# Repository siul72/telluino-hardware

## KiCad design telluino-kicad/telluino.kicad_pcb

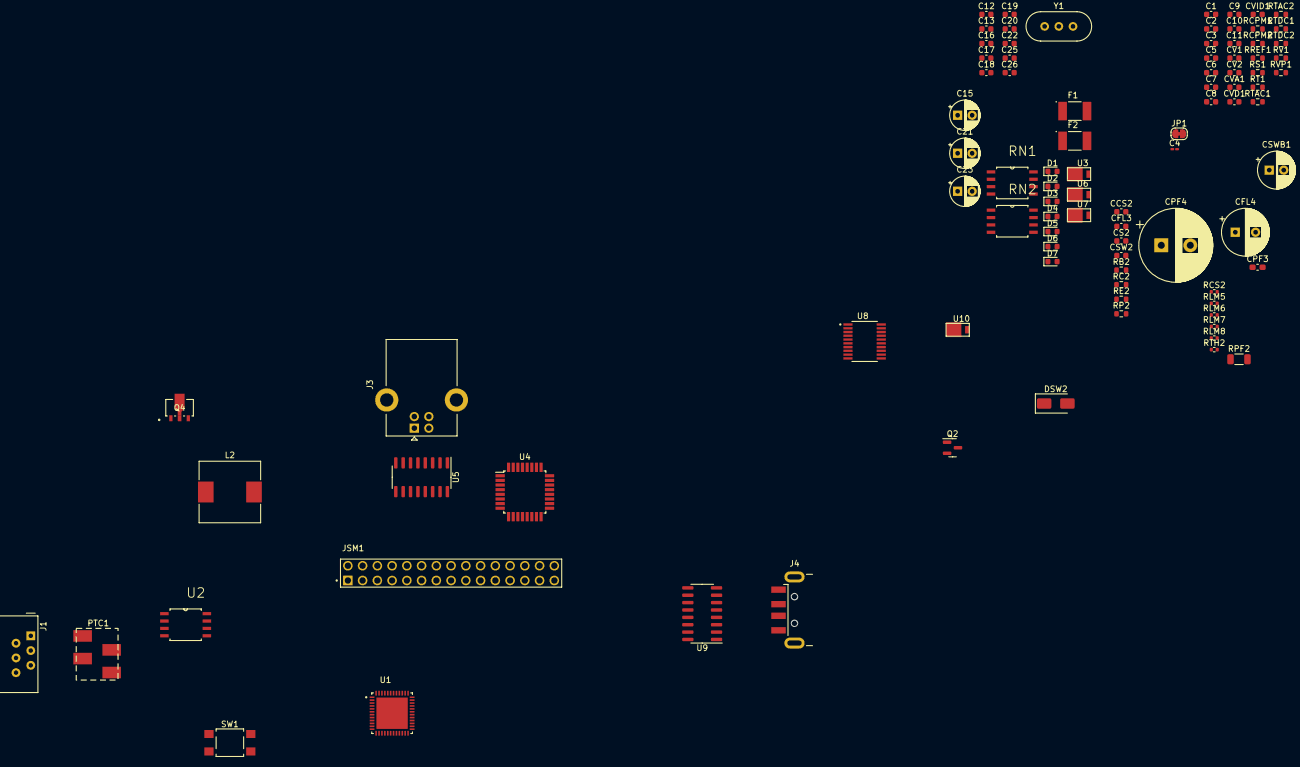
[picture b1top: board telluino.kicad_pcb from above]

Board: 2 copper layers, 92 parts (0 on the bottom side), 88 nets, no tracks yet.

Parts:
C1: 0.1 uF/100V; C_0603_1608Metric
C2, C3, C5, C6: 22 nF/100V; C_0603_1608Metric
C4: 22 nF/100V; C_0201_0603Metric_Pad0.64x0.40mm_HandSolder
C7, C11: 0.1 uF/16V; C_0603_1608Metric
C8, C9, C10: 4.7 uF/8.3V; C_0603_1608Metric
C12, C13, C25, C26: 0.1uF; C_0603_1608Metric
C15, C21, C23: 10uF_16V; CP_Radial_D5.0mm_P2.50mm
C16, C17, C22: 100nF; C_0603_1608Metric
C18, C19, C20: 1uF; C_0603_1608Metric
CCS2: 220pF; C_0603_1608Metric
CFL3: 0.1uF/100V; C_0603_1608Metric
CFL4: 10uF/100V; CP_Radial_D8.0mm_P3.50mm
CPF3: 0.1uF/100V; C_0603_1608Metric_Pad1.08x0.95mm_HandSolder
CPF4: 47uF/100V; CP_Radial_D12.5mm_P5.00mm
CS2: 100nF/25V; C_0603_1608Metric
CSW2: 10uF/25V; C_0603_1608Metric
CSWB1: 220uF/25V; CP_Radial_D6.3mm_P2.50mm
CV1: 4.7uF/8.3V; C_0603_1608Metric
CV2: 1uF/8.3V; C_0603_1608Metric
CVA1: 0.1uF/16V; C_0603_1608Metric
CVD1: 0.01uF/16V; C_0603_1608Metric
CVID1: 0.1uF/18V; C_0603_1608Metric
D1: PWR Green; LED_0603_1608Metric
D2, D4: Red Rx; LED_0603_1608Metric
D3, D6: Green Tx; LED_0603_1608Metric
D5: RUN Blue; LED_0603_1608Metric
D7: OP Orange; LED_0603_1608Metric
DSW2: ES1C-13-F 1A/150V; D_SMA
F1, F2: MF-MSMF050-2; FUSM4632X85
J1: 6P2C; RJ12_Amphenol_54601
J3: USB_B; USB_B_Lumberg_2411_02_Horizontal
J4: USB_A; USB_A_CNCTech_1001-011-01101_Horizontal
JP1: A_D_Ground_Bridge; SolderJumper-2_P1.3mm_Bridged_RoundedPad1.0x1.5mm
JSM1: 77313-101-30LF; AMPHENOL_77313-101-30LF
L2: 47uH 1.5A; L_10.4x10.4_H4.8
PTC1: MF-SD013; ptc-4-mf-sd
Q2: MMBT3904; SOT-23
Q4: ZXTP2012Z; SOT-89-3_4P5X2P6_DIO
RB2: 1K; R_0603_1608Metric
RC2: 75R; R_0603_1608Metric
RCPM1, RCPM2: 1Meg 1%; R_0603_1608Metric
RCS2: 3.48K; R_0402_1005Metric
RE2: 75R 5%; R_0603_1608Metric
RLM5, RLM6, RLM7, RLM8: 1R0 1/16W; R_0402_1005Metric
RN1, RN2: 4*1K; SOIC127P780X210-8N
RP2: 10K; R_0603_1608Metric
RPF2: 20R; R_1206_3216Metric
RREF1: 75K 0.5%; R_0603_1608Metric
RS1: 1Meg 1%; R_0603_1608Metric
RT1: 47.5K 1%; R_0603_1608Metric
RTAC1, RTAC2: 10K 1%; R_0603_1608Metric
RTDC1, RTDC2: 1Meg 1%; R_0603_1608Metric
RTH2: 1K; R_0402_1005Metric
RV1: 2R0 5%; R_0603_1608Metric
RVP1: 0; R_0603_1608Metric
SW1: SW_Push; SW_SPST_TL3305A
U1: LE9641PQC; QFN50P700X700X90-49N
U2: TISP61089BDR-S; SOIC127P780X210-8N
U3, U6, U7, U10: SS1P3L; DO220AAL
U4: ATmega328P-A; TQFP-32_7x7mm_P0.8mm
U5, U9: CH340C; SOIC-16_3.9x9.9mm_P1.27mm
U8: TXS0108EPWRG4; SOP65P640X120-20N
Y1: 16MHz; Crystal_HC49-U-3Pin_Vertical

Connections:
3.3V: CSWB1.1, CV1.2, CVD1.2, CVID1.2, JSM1.01, JSM1.02, RP2.1, RV1.1, U1.14 (VDDSW), U1.15 (DVDD), U1.23 (VDDHPI), U1.24 (*ZSI), U7.P$1 (K), U8.2 (VCCA), U8.10 (OE), U10.P$1 (K)
+3.3VA: C12.2, CV2.2, CVA1.2, RV1.2, U1.2 (AVDD1), U1.35 (AVDD2), U5.4 (V3), U7.P$2 (A)
+3.3VP: C26.2, U9.4 (V3), U10.P$2 (A)
+5V: C18.2, C19.2, C20.2, C21.1, CSW2.1, JSM1.29, JSM1.30, Q4.3, RB2.1, RN1.3 (R3.1), RN1.4 (R4.1), RN2.5 (R4.2), RN2.6 (R3.2), RN2.7 (R2.2), RN2.8 (R1.2), RS1.2, U3.P$1 (K), U4.4 (VCC), U4.6 (VCC), U4.18 (AVCC), U5.16 (VCC), U6.P$1 (K), U8.19 (VCCB), U9.16 (VCC)
+5VL: C15.1, C16.2, F1.2, U6.P$2 (A)
+5VP: C22.2, C23.1, F2.2, U3.P$2 (A)
/arduino_controller/RESET*: C13.2, C25.2, RN1.6 (R3.2), SW1.1, U4.29 (~RESET/PC6)
/arduino_controller/RUN: RN1.2 (R2.1), U4.13 (PB1)
ADC6: JSM1.23, U4.19 (ADC6)
ADC7: JSM1.25, U4.22 (ADC7)
AGND: C1.2, C5.2, C6.1, C7.1, C9.2, C10.2, C11.1, CSW2.2, CSWB1.2, CV1.1, CV2.1, CVA1.1, CVD1.1, CVID1.1, JP1.1 (A), RREF1.2, U1.49 (GND), U2.6 (A), U2.7 (A)
CS_N: U1.29 (*CS), U8.3 (A2)
CS_N_5: JSM1.08, U4.14 (PB2(*SS)), U8.18 (B2)
DCLK: U1.26 (DCLK), U8.1 (A1)
DCLK_5: JSM1.04, U4.17 (PB5(SCK)), U8.20 (B1)
DGND: C12.1, C15.2, C16.1, C17.1, C18.1, C19.1, C20.1, C21.2, C22.1, C23.2, C26.1, CCS2.2, CFL3.2, CFL4.1, CPF3.2, CPF4.1, D1.1 (K), D5.1 (K), D7.1 (K), J3.4 (GND), J3.5 (Shield), J4.4 (GND), J4.5 (Shield), JP1.2 (B), JSM1.05, JSM1.06, JSM1.09, JSM1.10, JSM1.13, JSM1.14, JSM1.17, JSM1.18, JSM1.27, JSM1.28, RLM5.2, RLM6.2, RLM7.2, RLM8.2, RTH2.2, SW1.2, U4.3 (GND), U4.5 (GND), U4.21 (GND), U5.1 (GND), U8.11 (GND), U9.1 (GND), Y1.2
DIN: U1.27 (DIN), U8.4 (A3)
DIN_5: JSM1.12, U4.15 (PB3(MOSI)), U8.17 (B3)
DOUT: U1.28 (DOUT), U8.5 (A4)
DOUT_5: JSM1.16, U4.16 (PB4(MISO)), U8.16 (B4)
DRA: U1.20 (DRA/ZMOSI), U8.8 (A7)
DRA_5: JSM1.11, U4.27 (PC4(SDA)), U8.13 (B7)
DXA: U1.19 (DXA/ZMISO), U8.7 (A6)
DXA_5: JSM1.07, U4.26 (PC3), U8.14 (B6)
FS: U1.18 (FS/ZSYNC), U8.6 (A5)
FS_5: JSM1.03, U4.25 (PC2), U8.15 (B5)
INT_N: U1.25 (*INT), U4.32 (PD2(INT0))
unnamed: C2.2, RCPM2.1
unnamed: C3.2, RTAC1.1
unnamed: C4.2, RTAC2.1
unnamed: CS2.1, Q4.1, RB2.2, RC2.1
unnamed: D1.2 (A), RN1.5 (R4.2)
unnamed: D2.2 (A), RN2.1 (R1.1)
unnamed: D2.1 (K), U4.30 (PD0(RX0)), U5.2 (TXD)
unnamed: D3.2 (A), RN2.2 (R2.1)
unnamed: D3.1 (K), U4.31 (PD1(TX0)), U5.3 (RXD)
unnamed: D4.2 (A), RN2.4 (R4.1)
unnamed: D5.2 (A), RN1.7 (R2.2)
unnamed: D6.2 (A), RN2.3 (R3.1)
unnamed: D7.2 (A), RN1.8 (R1.2)
unnamed: DSW2.1, L2.1, Q4.2
unnamed: J1.1, PTC1.3 (R2), RTDC1.1
unnamed: J1.2, PTC1.1 (R1), RTDC2.1
unnamed: J3.3 (D+), U5.5 (UD+)
unnamed: J3.2 (D-), U5.6 (UD-)
unnamed: F1.1, J3.1 (VBUS)
unnamed: J4.3 (D+), U9.5 (UD+)
unnamed: J4.2 (D-), U9.6 (UD-)
unnamed: F2.1, J4.1 (VBUS)
unnamed: L2.2, RCS2.1, RLM5.1, RLM6.1, RLM7.1, RLM8.1
unnamed: Q2.3 (C), RC2.2
unnamed: Q2.2 (E), RE2.2
unnamed: C8.1, U1.5 (IHL1)
unnamed: RREF1.1, U1.33 (IREF)
unnamed: RS1.1, U1.31 (I/O1/VS1)
unnamed: C9.1, U1.10 (LFC)
unnamed: RTAC1.2, U1.7 (RAC1)
unnamed: RTDC1.2, U1.9 (RDC1)
unnamed: C4.1, C5.1, PTC1.2 (R1), U1.45 (RINGD1), U2.1 (K1), U2.8 (K1)
unnamed: RT1.1, U1.1 (RSN1)
unnamed: RT1.2, U1.3 (RTV1)
unnamed: RCPM2.2, U1.12 (SWCMPY)
unnamed: C2.1, RCPM1.2, U1.11 (SWVSY)
unnamed: RTAC2.2, U1.6 (TAC1)
unnamed: RTDC2.2, U1.8 (TDC1)
unnamed: C3.1, C6.2, PTC1.4 (R2), U1.46 (TIPD1), U2.4 (K2), U2.5 (K2)
unnamed: C7.2, U1.22 (DVDD1V2)
unnamed: C8.2, C10.1, U1.4 (VREF)
unnamed: C1.1, RVP1.2, U2.2 (G)
unnamed: C17.2, U4.20 (AREF)
unnamed: U4.7 (XTAL1/PB6), Y1.3
unnamed: U4.8 (XTAL2/PB7), Y1.1
unnamed: C13.1, U5.13 (~DTR)
unnamed: C25.1, U9.13 (~DTR)
PB0: RN1.1 (R1.1), U4.12 (PB0)
PC0: JSM1.19, U4.23 (PC0)
PC1: JSM1.21, U4.24 (PC1)
PCLK: U1.21 (PCLK/ZCLK), U8.9 (A8)
PCLK_5: JSM1.15, U4.28 (PC5(SCL)), U8.12 (B8)
PD2: JSM1.22, U4.1 (PD3(INT1))
PD4: D4.1 (K), U4.2 (PD4), U9.3 (RXD)
PD5: D6.1 (K), U4.9 (PD5), U9.2 (TXD)
PD6: JSM1.24, U4.10 (PD6)
PD7: JSM1.26, U4.11 (PD7)
SWISY: CCS2.1, RCS2.2, RTH2.1, U1.13 (SWISY)
SWOUTY: CS2.2, RE2.1, RP2.2, U1.16 (SWOUTY)
VBAT: C11.2, CPF3.1, CPF4.2, RPF2.2, RVP1.1, U1.48 (VBAT1)
VBSENSE: CFL3.1, CFL4.2, DSW2.2, RCPM1.1, RPF2.1

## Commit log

2023-05-10 schematics line driver done
2023-05-10 save
2023-05-13 before buck supply
2023-05-29 complete_Except_mc
2023-06-06 schematic done
2023-06-08 ready_placement
2023-06-08 half placed
2023-09-21 update ignore
